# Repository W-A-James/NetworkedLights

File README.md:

# NetworkedLights

Code for Control web-app lives in `app/`

KiCad project lives in `schematics/networked_lights`

Code for microcontroller lives in `microcontroller/NetworkedLights`

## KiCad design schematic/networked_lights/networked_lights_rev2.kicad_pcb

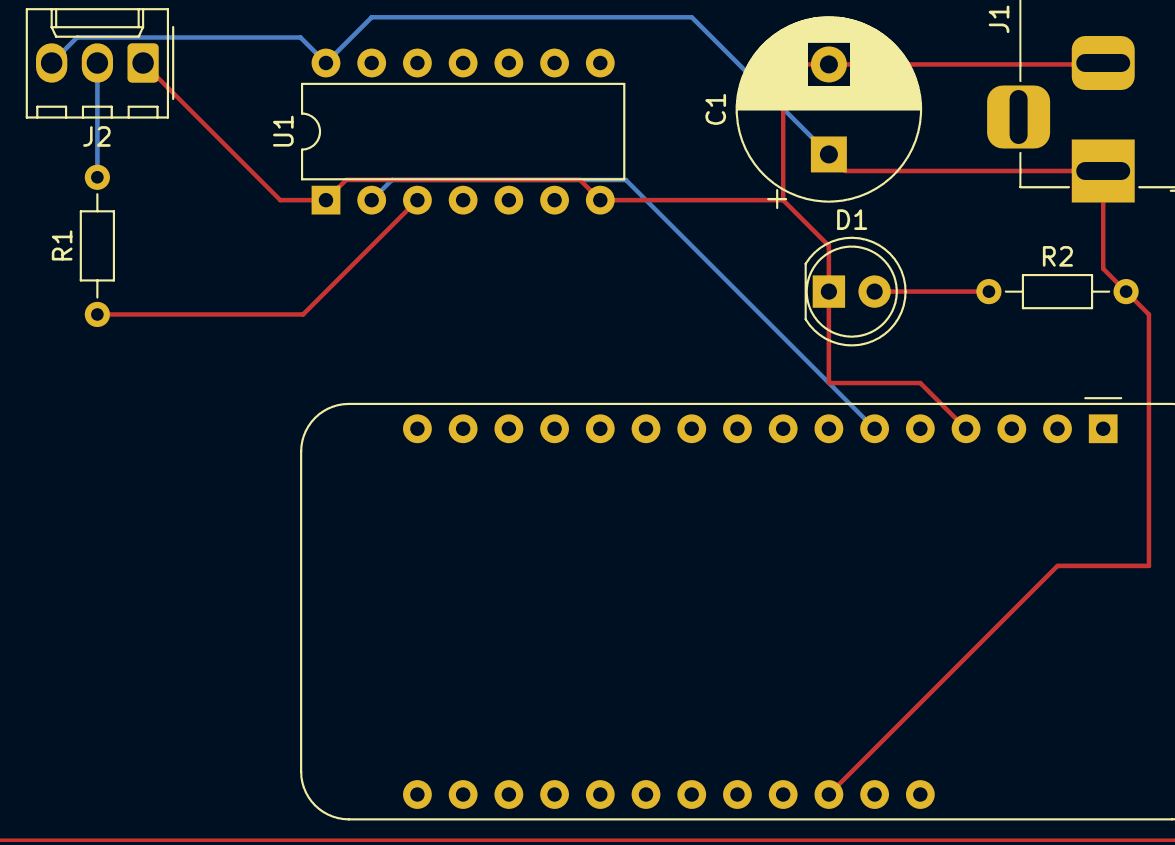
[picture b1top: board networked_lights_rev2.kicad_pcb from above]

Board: 2 copper layers, 8 parts (0 on the bottom side), 6 nets.

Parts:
A1: Adafruit_Feather_HUZZAH32_ESP32; Adafruit_Feather
C1: 1000uF; CP_Radial_D10.0mm_P5.00mm
D1: Power LED; LED_D5.0mm
J1: Barrel_Jack; BarrelJack_Horizontal
J2: Conn_01x03_Male; Molex_KK-254_AE-6410-03A_1x03_P2.54mm_Vertical
R1: 250; R_Axial_DIN0204_L3.6mm_D1.6mm_P7.62mm_Horizontal
R2: 1k; R_Axial_DIN0204_L3.6mm_D1.6mm_P7.62mm_Horizontal
U1: SN74AHCT125N; DIP-14_W7.62mm

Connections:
+5V: A1.26 (USB), C1.1, J1.1, J2.3, R2.2, U1.14 (VCC)
/light_string/DIN: J2.2, R1.2
GND: A1.4 (GND), C1.2, D1.1 (K), J1.2, J2.1, U1.1 (*1OE), U1.7 (GND)
unnamed: A1.6 (DAC1/A1), U1.2 (1A)
unnamed: D1.2 (A), R2.1
unnamed: R1.1, U1.3 (1Y)

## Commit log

2023-10-26 Initial
2023-10-27 Progress
2023-10-27 First draft complete
2023-10-27 Remove environment variable defaulting
2023-10-27 Update page
2023-10-27 project restructure
2023-10-27 update package files
2023-10-27 poll for status more often
2023-10-27 Initial
    Progress
    First draft complete
    Remove environment variable defaulting
    Update page
    project restructure
    update package files
2023-11-01 convert to TS
2023-11-01 update config files
2024-03-12 update error handling
2024-03-12 add bootstrap css
2024-03-12 update front-end js
2024-03-13 redo styling
2024-03-13 fixes
2024-03-13 update tsconfig
2024-03-13 add image of schematics
2024-03-13 add image
2024-03-13 update lockfile
2024-03-13 remove unneeded files
2024-03-13 disable incomplete colour selector
2024-03-13 fix on button
2024-03-13 lint fix
2024-03-13 update styling
2024-03-13 revert styling
2024-03-15 add header
2024-03-15 start go server refactor
2024-03-19 reorganize server
2024-03-19 add gitignore
2024-03-20 make sliders easier to use
2024-03-20 Update comments
2024-03-20 Update eslintrc
2024-04-09 add status message tests
2024-04-09 misc updates
2024-04-09 update server
2024-09-28 update sketch.yaml and linting
2024-09-28 remove go_server
2024-09-28 add .gitignore
2024-09-28 add media
2024-09-28 cleanup
2024-09-28 test cleanup
2024-09-28 convert to async/await
2024-09-28 move main server logic to encapsulated class
2024-09-28 use ISO datetime string for logging
2024-09-28 Check memory usage
2024-10-25 ensure payload is sending correct types
2025-01-12 start react refactor
2025-01-13 First draft react refactor
2025-01-13 add debugging logic
2025-01-13 remove old server
2025-01-13 update packaged name and clean up tsx
2025-01-13 reorganization
2025-02-11 add logo
2025-02-11 fix variable shadowing
2025-02-11 update client lockfile
